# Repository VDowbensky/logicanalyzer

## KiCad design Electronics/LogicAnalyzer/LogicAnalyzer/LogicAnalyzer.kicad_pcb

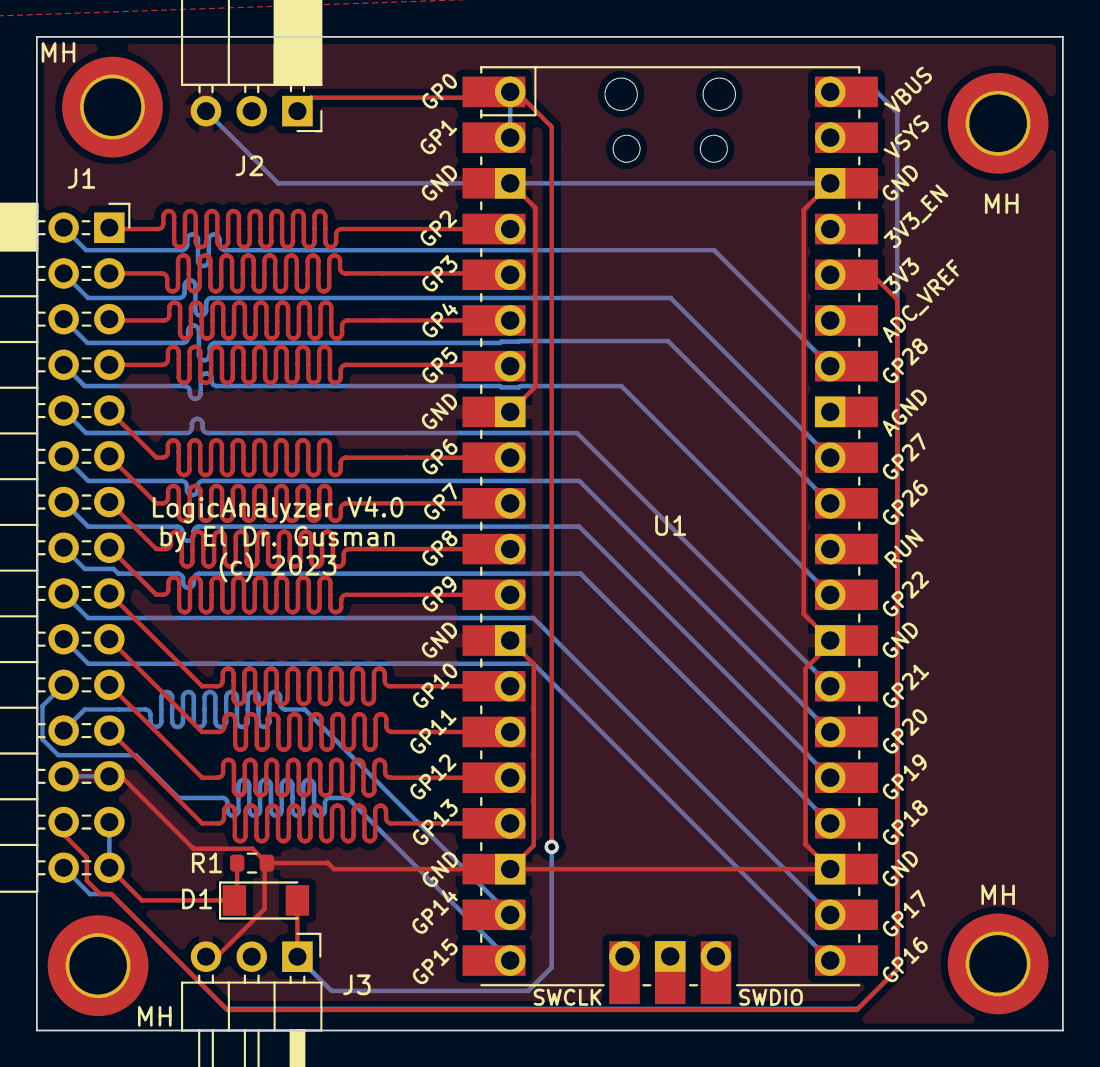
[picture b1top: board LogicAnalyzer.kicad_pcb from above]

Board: 2 copper layers, 57.0 x 55.2 mm, 10 parts (0 on the bottom side), 29 nets.

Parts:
D1: LL4148; D_MiniMELF
J1: Conn_02x15_Odd_Even; PinSocket_2x15_P2.54mm_Horizontal
J2: Conn_01x03; PinSocket_1x03_P2.54mm_Horizontal
J3: Conn_01x03; PinHeader_1x03_P2.54mm_Horizontal
MH: MountingHole_3.2mm_M3_DIN965_Pad_TopBottom
MH#2, MH#3, MH#4: MountingHole_3.2mm_M3_DIN965_Pad_TopBottom
R1: 100k; R_0603_1608Metric
U1: Pico; RPi_Pico_SMD_TH

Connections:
/3V3: J1.28, U1.36 (3V3)
/5V: J1.30, U1.40 (VBUS)
/CHAN_0: J1.1, U1.4 (GPIO2)
/CHAN_1: J1.3, U1.5 (GPIO3)
/CHAN_2: J1.5, U1.6 (GPIO4)
/CHAN_3: J1.7, U1.7 (GPIO5)
/CHAN_4: J1.9, U1.9 (GPIO6)
/CHAN_5: J1.11, U1.10 (GPIO7)
/CHAN_6: J1.13, U1.11 (GPIO8)
/CHAN_7: J1.15, U1.12 (GPIO9)
/CHAN_8: J1.17, U1.14 (GPIO10)
/CHAN_9: J1.19, U1.15 (GPIO11)
/CHAN_10: J1.21, U1.16 (GPIO12)
/CHAN_11: J1.23, U1.17 (GPIO13)
/CHAN_12: J1.24, U1.19 (GPIO14)
/CHAN_13: J1.22, U1.20 (GPIO15)
/CHAN_14: J1.20, U1.21 (GPIO16)
/CHAN_15: J1.18, U1.22 (GPIO17)
/CHAN_16: J1.16, U1.24 (GPIO18)
/CHAN_17: J1.14, U1.25 (GPIO19)
/CHAN_18: J1.12, U1.26 (GPIO20)
/CHAN_19: J1.10, U1.27 (GPIO21)
/CHAN_20: J1.8, U1.29 (GPIO22)
/CHAN_21: J1.6, U1.31 (GPIO26_ADC0)
/CHAN_22: J1.4, U1.32 (GPIO27_ADC1)
/CHAN_23: J1.2, U1.34 (GPIO28_ADC2)
/EXT_CHAIN: D1.2 (A), J2.1, J3.1, U1.1 (GPIO0), U1.2 (GPIO1)
/EXT_T: D1.1 (K), J1.27, J1.29, R1.1
/GND: J1.25, J1.26, J2.3, J3.3, R1.2, U1.3 (GND), U1.8 (GND), U1.13 (GND), U1.18 (GND), U1.23 (GND), U1.28 (GND), U1.38 (GND)

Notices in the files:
Electronics/LogicAnalyzer/LogicAnalyzer/LogicAnalyzer.kicad_pcb:
(c) 2023
